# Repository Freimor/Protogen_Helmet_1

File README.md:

## Protogen Helmet for Wolfy

My first try to make protogen helmet. This design referenced to Kaiborg Studios LED helmet, but only conceptually. Overall design - 3d model of helmet, visor vacuum forming, PCB design - completely new. 

*what PCB contained, other electronics used*

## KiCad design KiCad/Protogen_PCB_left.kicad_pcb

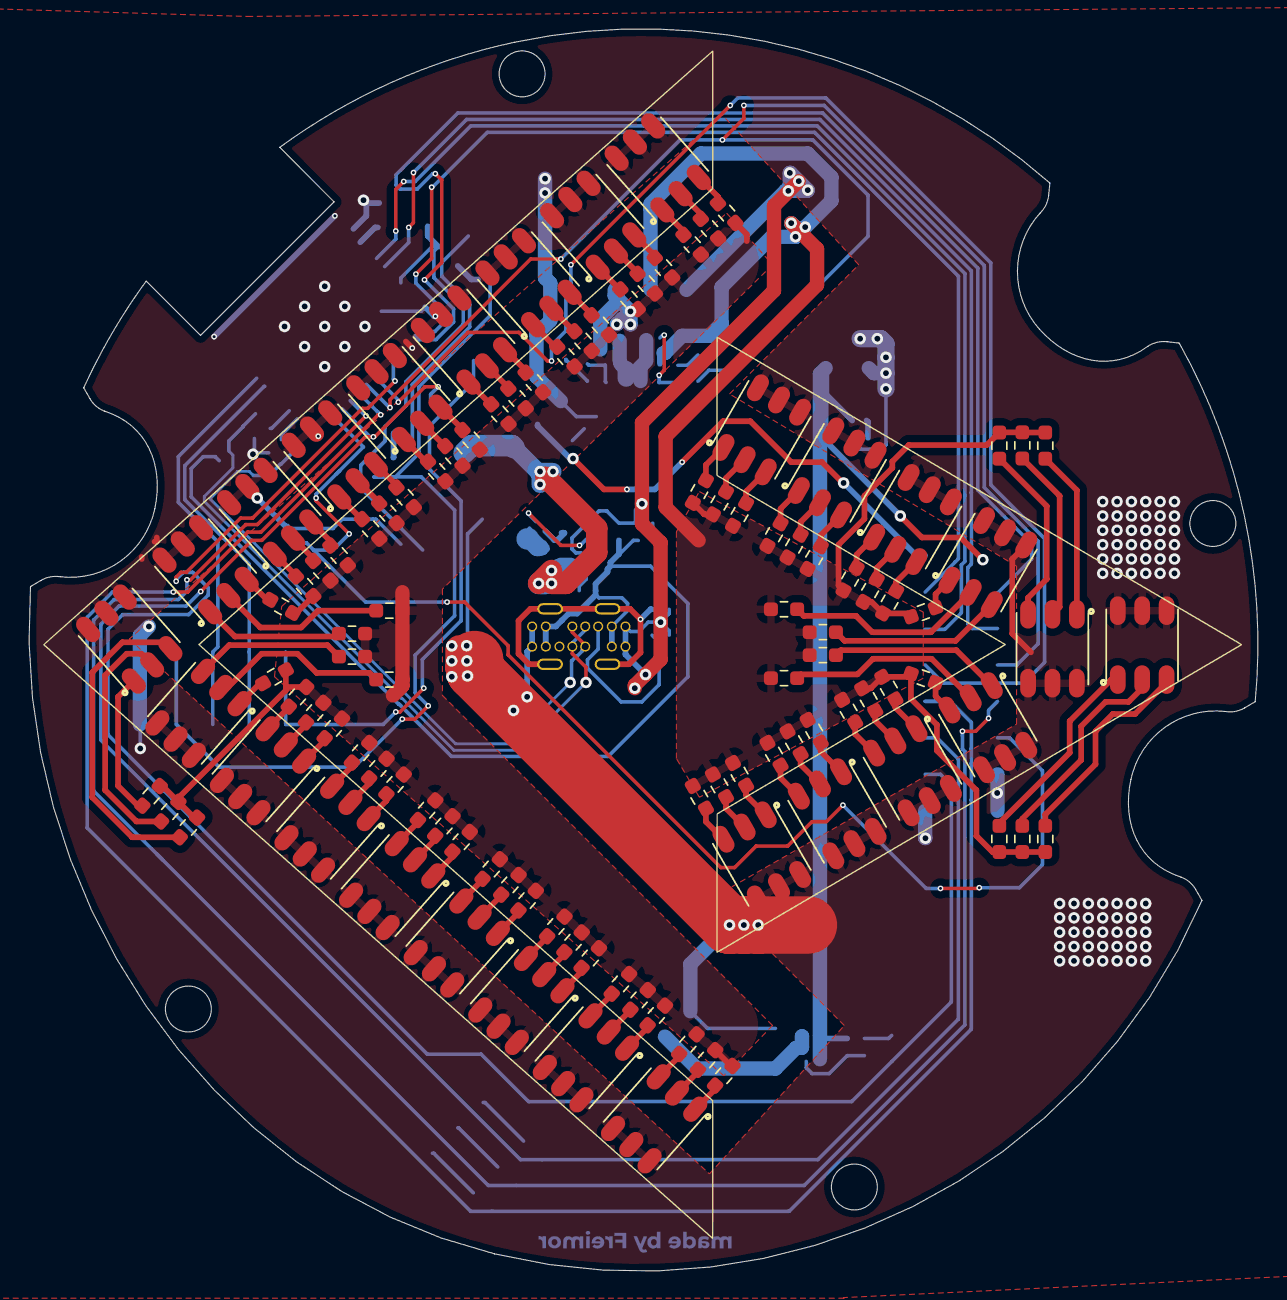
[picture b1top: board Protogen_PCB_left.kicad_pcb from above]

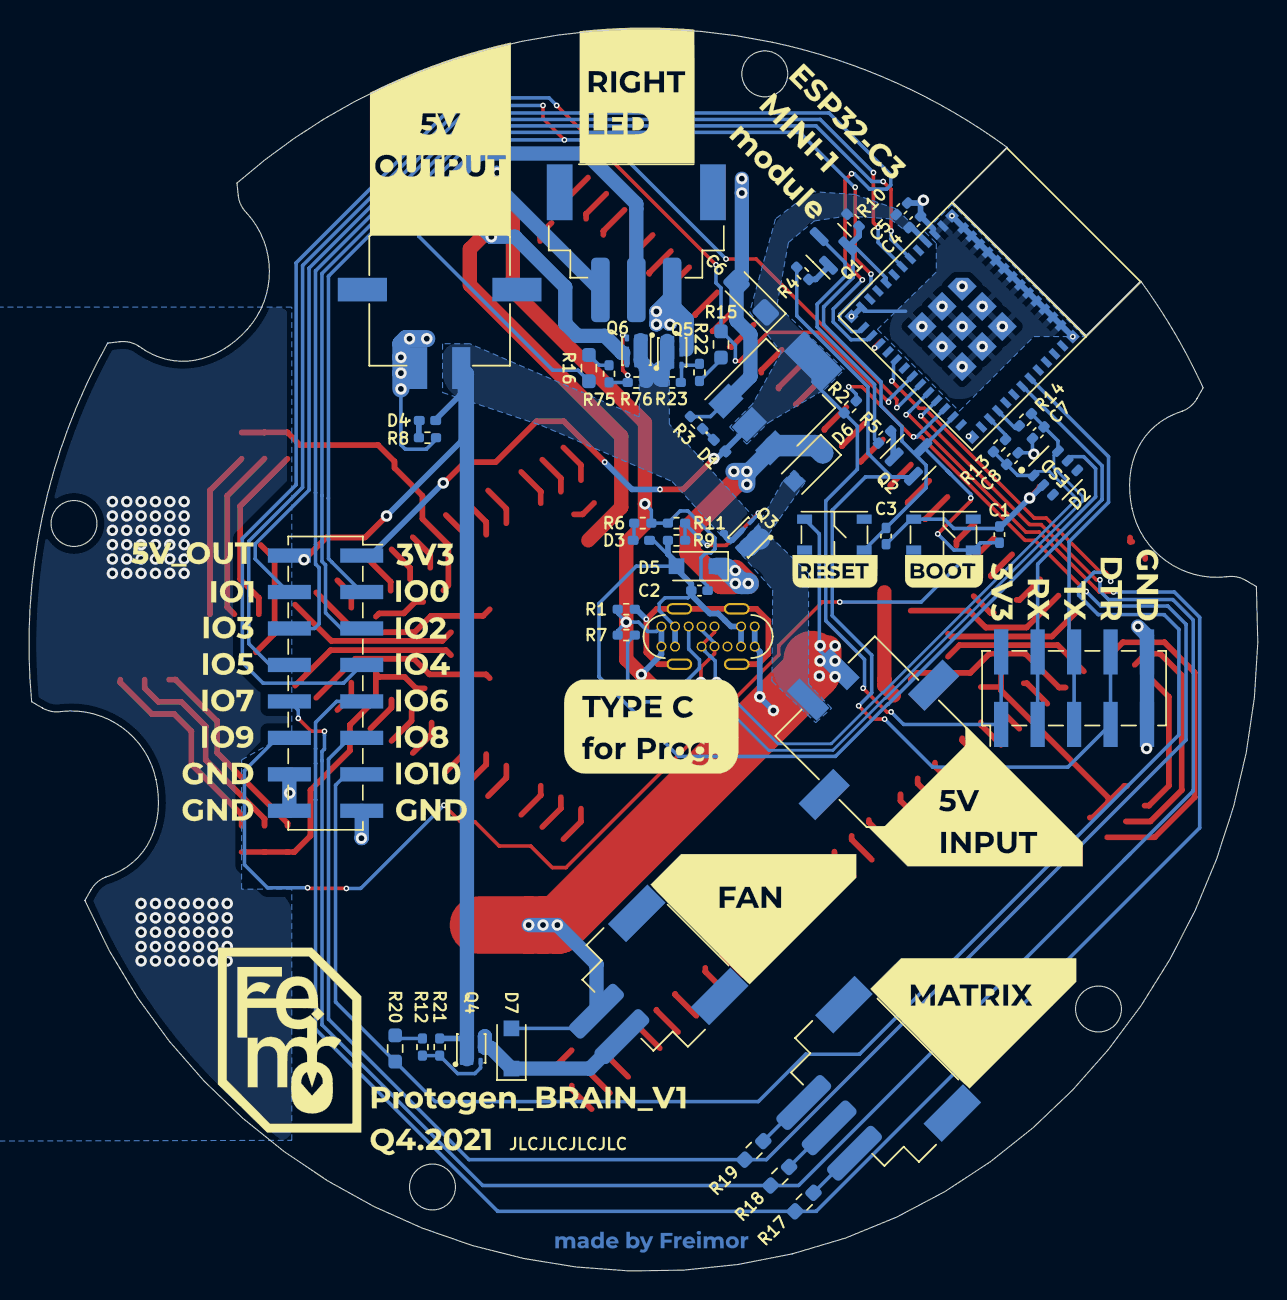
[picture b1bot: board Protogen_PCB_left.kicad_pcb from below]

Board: 2 copper layers, 85.6 x 86.5 mm, 168 parts (58 on the bottom side), 127 nets.

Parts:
BOOT: PTS810SJ; SW_SMD_C&K_(PTS810SJ)
C1, C3, C5: 100nF; C_0402_1005Metric_Pad0.74x0.62mm_HandSolder
C2, C4: 10uF; C_0402_1005Metric_Pad0.74x0.62mm_HandSolder
C6: 22uF; CP_EIA-3216-18_Kemet-A_Pad1.58x1.35mm_HandSolder
C7, C8: 22pF; C_0402_1005Metric_Pad0.74x0.62mm_HandSolder
D1, D3, D4: LED; LED_0402_1005Metric_Pad0.77x0.64mm_HandSolder
D2: IP4220CZ6
D5, D6, D7: D; D_SOD-123F
D8, D9, D10, D11, D12, D13, D14, D15, D16, D17, D18, D19, D20, D21, D22, D23, D24: LED_GREEN; LED_5050_HL-AF-5060
D25, D26, D27, D28, D29, D30, D31, D32, D33, D34: LED_BLUE; LED_5050_HL-AF-5060
J1: USB_C_Receptacle_USB2.0; USB_C_Receptable_918-418K2022Y40000
J2: INPUT_POWER; Conn_XKB_MX3_X3025WRS-02
J3: Conn_01x16_Male; PinSocket_2x08_P2.54mm_Vertical_SMD
J4: CONN_SIDE_LED; Conn_XKB_XH2.54_3pin_(X8821WRS-03)
J5: OUTPUT_POWER; Conn_XKB_MX3_X3025WRS-02
J6: UART; PinHeader_2x05_P2.54mm_Vertical_SMD
J7: CONN_MATRIX; Conn_XKB_XH2.54_3pin_(X8821WRS-03)
J8: FAN; Conn_XKB_XH2.54_2pin_(X8821WRS-02)
Q1, Q2: L8050; SOT-23
Q3, Q4, Q5, Q6: HSCB2307(P_Mosfet_8A_20V); HSCB2307
R1: 1M; R_0402_1005Metric_Pad0.72x0.64mm_HandSolder
R2, R4, R5, R10, R11, R21, R23, R76: 10k; R_0402_1005Metric_Pad0.72x0.64mm_HandSolder
R3, R6, R8, R9, R12, R22, R75: 1k; R_0402_1005Metric_Pad0.72x0.64mm_HandSolder
R7: 5k1; R_0402_1005Metric_Pad0.72x0.64mm_HandSolder
R13, R14: 22; R_0402_1005Metric_Pad0.72x0.64mm_HandSolder
R15, R16, R17, R18, R19, R20: 0; R_0603_1608Metric_Pad0.98x0.95mm_HandSolder
R24, R25, R26, R27, R28, R29, R30, R31, R32, R33, R34, R35, R36, R37, R38, R39, R40, R41, R42, R43, R44, R45, R46, R47, R48, R49, R50, R51, R52, R53, R54, R55, R56, R57, R58, R59, R60, R61, R62, R63, R64, R65, R66, R67, R68, R69, R70, R71, R72, R73, R74, R77, R78, R79, R80, R81, R82, R83, R84, R85, R86, R87, R88, R89, R90, R91, R92, R93, R94, R95, R96, R97, R98, R99, R100, R101, R102, R103, R104, R105, R106: 300; R_0603_1608Metric_Pad0.98x0.95mm_HandSolder
RESET: PTS810SJ; SW_SMD_C&K_(PTS810SJ)
Ref**: Val**; Headphone_right_silk
Ref_silk: Val**; Wolfy_headphone_left_PCB
U1: AMS1117-3.3; SOT-223-3_TabPin2
U2: ESP32-C3-MINI-1-N4; ESP32-C3-MINI-1

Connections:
3v3: C4.1, C5.1, C6.1, D1.2, J3.1, J6.1, J6.2, R2.1, R10.1, U1.2, U2.3
5v_INPUT: D6.2, J2.1, Q3.1, Q3.2, Q3.5, Q3.6, Q3.8
5v_OUTPUT: D4.2, J3.2, J5.1, Q3.4, Q3.7, Q4.1, Q4.2, Q4.5, Q4.6, Q4.8, Q5.1, Q5.2, Q5.5, Q5.6, Q5.8, Q6.1, Q6.2, Q6.5, Q6.6, Q6.8, R21.1, R23.1, R76.1
BLUE_LED_ANODE: J4.2, Q6.4, Q6.7, R77.2, R78.2, R79.2, R80.2, R81.2, R82.2, R83.2, R84.2, R85.2, R86.2, R87.2, R88.2, R89.2, R90.2, R91.2, R92.2, R93.2, R94.2, R95.2, R96.2, R97.2, R98.2, R99.2, R100.2, R101.2, R102.2, R103.2, R104.2, R105.2, R106.2
D+: C7.1, D2.6, J1.A6, J1.B6, R14.1
D-: C8.1, D2.1, J1.A7, J1.B7, R13.1
DTR: J6.7, J6.8, Q2.2, R4.2
EN: C3.1, Q1.2, R10.2, RESET.4, U2.8
GND: BOOT.1, C1.2, C2.2, C3.2, C4.2, C5.2, C6.2, C7.2, C8.2, D2.2, D7.2, D8.4, D8.5, D8.6, D9.4, D9.5, D9.6, D10.4, D10.5, D10.6, D11.4, D11.5, D11.6, D12.4, D12.5, D12.6, D13.4, D13.5, D13.6, D14.4, D14.5, D14.6, D15.4, D15.5, D15.6, D16.4, D16.5, D16.6, D17.4, D17.5, D17.6, D18.4, D18.5, D18.6, D19.4, D19.5, D19.6, D20.4, D20.5, D20.6, D21.4, D21.5, D21.6, D22.4, D22.5, D22.6, D23.4, D23.5, D23.6, D24.4, D24.5, D24.6, D25.4, D25.5, D25.6, D26.4, D26.5, D26.6, D27.4, D27.5, D27.6, D28.4, D28.5, D28.6, D29.4, D29.5, D29.6, D30.4, D30.5, D30.6, D31.4, D31.5, D31.6, D32.4, D32.5, D32.6, D33.4, D33.5, D33.6, D34.4, D34.5, D34.6, J1.A1, J2.2, J3.14, J3.15, J3.16, J4.3, J5.2, J6.9, J6.10, J8.2, R1.2, R3.2, R6.2, R7.2, R8.2, R11.2, RESET.1, U1.1, U2.1, U2.2, U2.11, U2.14, U2.36, U2.37, U2.38, U2.39, U2.40, U2.41, U2.42, U2.43, U2.44, U2.45, U2.46, U2.47, U2.48, U2.49, U2.50, U2.51, U2.52, U2.53
GREEN_LED_ANODE: J4.1, Q5.4, Q5.7, R24.2, R25.2, R26.2, R27.2, R28.2, R29.2, R30.2, R31.2, R32.2, R33.2, R34.2, R35.2, R36.2, R37.2, R38.2, R39.2, R40.2, R41.2, R42.2, R43.2, R44.2, R45.2, R46.2, R47.2, R48.2, R49.2, R50.2, R51.2, R52.2, R53.2, R54.2, R55.2, R56.2, R57.2, R58.2, R59.2, R60.2, R61.2, R62.2, R63.2, R64.2, R65.2, R66.2, R67.2, R68.2, R69.2, R70.2, R71.2, R72.2, R73.2, R74.2
IO0: J3.3, U2.12
IO1: J3.4, U2.13
IO2: J3.5, U2.5
IO3: J3.6, U2.6
IO4: J3.7, R15.2, U2.18
IO4_GREEN_LED: R15.1, R22.2
IO5: J3.8, R16.2, U2.19
IO5_BLUE_LED: R16.1, R75.2
IO6: J3.9, R17.2, U2.20
IO6_Matrix_SPI_DATA: J7.1, R17.1
IO7: J3.10, R18.2, U2.21
IO7_Matrix_SPI_SCK: J7.2, R18.1
IO8: J3.11, R2.2, R19.2, U2.22
IO8_Matrix_SPI_CS: J7.3, R19.1
IO9: BOOT.4, C1.1, J3.12, Q2.3, U2.23
IO10: J3.13, R20.2, U2.16
IO10_FAN: R12.2, R20.1
unnamed: D1.1, R3.1
unnamed: D3.1, R6.1
unnamed: D4.1, R8.1
unnamed: D5.1, D6.1, U1.3
unnamed: D7.1, J8.1, Q4.4, Q4.7
unnamed: D8.1, R24.1
unnamed: D8.2, R25.1
unnamed: D8.3, R26.1
unnamed: D9.1, R27.1
unnamed: D9.2, R28.1
unnamed: D9.3, R29.1
unnamed: D10.1, R30.1
unnamed: D10.2, R31.1
unnamed: D10.3, R32.1
unnamed: D11.1, R33.1
unnamed: D11.2, R34.1
unnamed: D11.3, R35.1
unnamed: D12.1, R36.1
unnamed: D12.2, R37.1
unnamed: D12.3, R38.1
unnamed: D13.1, R39.1
unnamed: D13.2, R40.1
unnamed: D13.3, R41.1
unnamed: D14.1, R42.1
unnamed: D14.2, R43.1
unnamed: D14.3, R44.1
unnamed: D15.1, R45.1
unnamed: D15.2, R46.1
unnamed: D15.3, R47.1
unnamed: D16.1, R48.1
unnamed: D16.2, R49.1
unnamed: D16.3, R50.1
unnamed: D17.1, R51.1
unnamed: D17.2, R52.1
unnamed: D17.3, R53.1
unnamed: D18.1, R54.1
unnamed: D18.2, R55.1
unnamed: D18.3, R56.1
unnamed: D19.1, R57.1
unnamed: D19.2, R58.1
unnamed: D19.3, R59.1
unnamed: D20.1, R60.1
unnamed: D20.2, R61.1
unnamed: D20.3, R62.1
unnamed: D21.1, R63.1
unnamed: D21.2, R64.1
unnamed: D21.3, R65.1
unnamed: D22.1, R66.1
unnamed: D22.2, R67.1
unnamed: D22.3, R68.1
unnamed: D23.1, R69.1
unnamed: D23.2, R70.1
unnamed: D23.3, R71.1
unnamed: D24.1, R72.1
unnamed: D24.2, R73.1
unnamed: D24.3, R74.1
unnamed: D25.1, R77.1
unnamed: D25.2, R78.1
unnamed: D25.3, R79.1
unnamed: D26.1, R80.1
unnamed: D26.2, R81.1
unnamed: D26.3, R82.1
unnamed: D27.1, R83.1
unnamed: D27.2, R84.1
unnamed: D27.3, R85.1
unnamed: D28.1, R86.1
unnamed: D28.2, R87.1
unnamed: D28.3, R88.1
unnamed: D29.1, R89.1
unnamed: D29.2, R90.1
unnamed: D29.3, R91.1
unnamed: D30.1, R92.1
unnamed: D30.2, R93.1
unnamed: D30.3, R94.1
unnamed: D31.1, R95.1
unnamed: D31.2, R96.1
unnamed: D31.3, R97.1
unnamed: D32.1, R98.1
unnamed: D32.2, R99.1
unnamed: D32.3, R100.1
unnamed: D33.1, R101.1
unnamed: D33.2, R102.1
unnamed: D33.3, R103.1
unnamed: D34.1, R104.1
unnamed: D34.2, R105.1
unnamed: D34.3, R106.1
unnamed: J1.A5, R7.1
unnamed: J1.S1, R1.1
unnamed: Q1.1, R4.1
unnamed: Q2.1, R5.1
unnamed: Q3.3, R9.1, R11.1
unnamed: Q4.3, R12.1, R21.2
unnamed: Q5.3, R22.1, R23.2
unnamed: Q6.3, R75.1, R76.2
unnamed: R13.2, U2.26
unnamed: R14.2, U2.27
RESET: Q1.3, R5.2
RX: J6.3, J6.4, U2.30
TX: J6.5, J6.6, U2.31
VBUS: C2.1, D2.5, D3.2, D5.2, J1.A4, R9.2

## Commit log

2022-10-17 Upload all files
